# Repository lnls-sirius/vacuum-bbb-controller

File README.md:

# vacuum-bbb-controller
Graphical interface [./software/pydm/pydm_1.2/README.md](./software/pydm/pydm_1.2/README.md)

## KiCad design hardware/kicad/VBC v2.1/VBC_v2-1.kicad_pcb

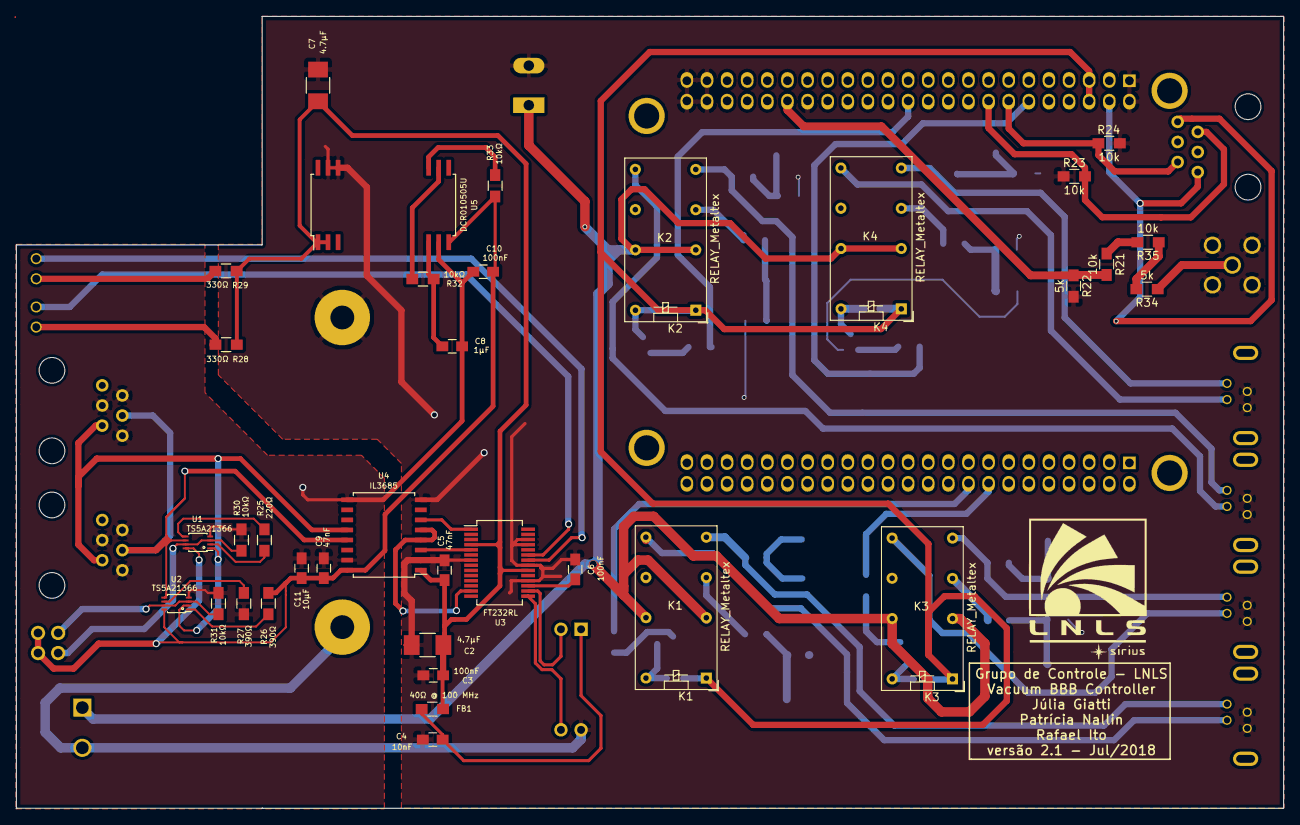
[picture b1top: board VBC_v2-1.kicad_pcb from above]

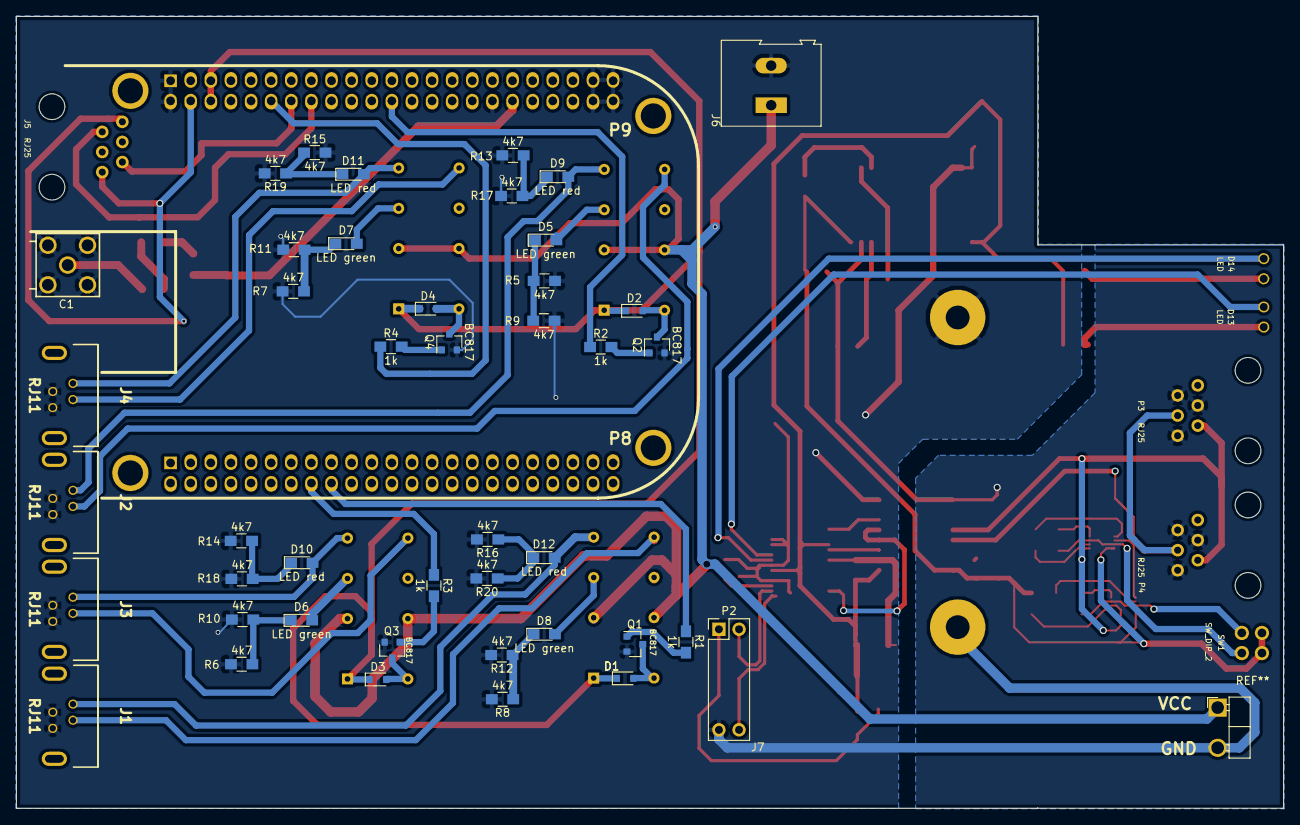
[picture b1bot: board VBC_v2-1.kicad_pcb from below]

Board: 2 copper layers, 160.0 x 100.1 mm, 85 parts (50 on the bottom side), 63 nets.

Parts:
C1: SMA_Molex_73251-2201
C2, C7: 4.7µF; C_1210_HandSoldering
C3, C6, C10: 100nF; C_0805_HandSoldering
C4: 10nF; C_0805_HandSoldering
C5, C9: 47nF; C_0805_HandSoldering
C8: 1µF; C_0805_HandSoldering
C11: 10µF; C_0805_HandSoldering
D1, D2, D3, D4: D; D_0805
D5, D6, D7, D8: LED green; LED_0805_HandSoldering
D9, D10, D11, D12: LED red; LED_0805_HandSoldering
D13, D14: LED; LED_para_painel_KINGBRIGHT
FB1: 40Ω @ 100 MHz; R_0805_HandSoldering
J1, J2, J3, J4: RJ11; RJ11-4P4C-HIROSE_2
J5: RJ25; RJ25_(conversor)
J6: TerminalBlock_Altech_AK300-2_P5.00mm
J7: Conn_01x01; Mean_Well_RS15
K1, K2, K3, K4: RELAY_Metaltex; Relay_DPDT_Omron_G5V-2
P2: USB Mini-B; Pin_Header_Straight_2x06_Pitch2.54mm
P3, P4: RJ25
Q1, Q2, Q3, Q4: BC817; SOT-23
R1, R2, R3, R4: 1k; R_0805_HandSoldering
R5, R6, R7, R8, R9, R10, R11, R12, R13, R14, R15, R16, R17, R18, R19, R20: 4k7; R_0805_HandSoldering
R21, R23, R24, R35: 10k; R_0805_HandSoldering
R22, R34: 5k; R_0805_HandSoldering
R25: 220Ω; R_0805_HandSoldering
R26, R27: 390Ω; R_0805_HandSoldering
R28, R29: 330Ω; R_0805_HandSoldering
R30, R31, R32, R33: 10kΩ; R_0805_HandSoldering
SW1: SW_DIP_2; DIP_switch_(2_positions)
U1, U2: TS5A21366; VSSOP-8
U3: FT232RL; SSOP-28_5.3x10.2mm_Pitch0.65mm
U4: IL3685; SOIC-16_7.5x10.3mm_Pitch1.27mm
U5: DCR010505U

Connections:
+5V: C2.1, C3.1, C5.1, C7.1, FB1.1, R28.1, R29.1, U3.4, U3.20, U4.1, U5.1, U5.2
+24V: J6.1, K1.4, K1.13, K2.4, K2.13, K3.4, K3.13, K4.4, K4.13
/3.3V_BBB: J5.1, J5.6
/AIn_BBB: R21.2, R22.1
/BBB_p5: J5.5, R24.1
/BBB_p6: J5.2, R23.2
/USB_converter_485./5V_ISOLATED: C9.1, C10.1, C11.1, R26.2, R33.1, SW1.1, SW1.3, U1.8, U2.8, U4.16, U5.14
/USB_converter_485./GND_ISOLATED: C8.2, C9.2, C10.2, C11.2, P3.1, P3.4, P3.5, P4.1, P4.4, P4.5, R27.2, R30.1, R31.1, U1.4, U2.4, U4.9, U4.15, U5.13
/USB_converter_485./RS485+: P3.2, P4.2, U1.1, U2.2, U4.12
/USB_converter_485./RS485-: P3.3, P4.3, U1.6, U2.5, U4.13
/USB_converter_485./RXD: U3.5, U4.3
/USB_converter_485./RXLED#: D14.1, U3.22
/USB_converter_485./TXD: U3.1, U4.6
/USB_converter_485./TXDEN: U3.13, U4.4, U4.5
/USB_converter_485./TXLED#: D13.1, U3.23
/USB_converter_485./USB_D+: P2.3, U3.15
/USB_converter_485./USB_D-: P2.2, U3.16
GND: C1.2, C2.2, C3.2, C4.2, C5.2, C6.2, C7.2, J1.2, J1.4, J2.2, J2.4, J3.2, J3.4, J4.2, J4.4, J6.2, J7.1, J7.2, P2.5, Q1.2, Q2.2, Q3.2, Q4.2, R5.2, R6.2, R7.2, R8.2, R9.2, R10.2, R11.2, R12.2, R13.2, R14.2, R15.2, R16.2, R17.2, R18.2, R19.2, R20.2, R22.2, R23.1, R24.2, U3.7, U3.18, U3.21, U3.25, U3.26, U4.2, U4.8, U5.26, U5.27
unnamed: C1.1, R34.1
unnamed: C4.1, FB1.2, P2.1
unnamed: C6.1, U3.17
unnamed: C8.1, R32.1, U5.12
unnamed: D1.2, K1.16, Q1.3
unnamed: D2.2, K2.16, Q2.3
unnamed: D3.2, K3.16, Q3.3
unnamed: D4.2, K4.16, Q4.3
unnamed: D5.1, R5.1, R9.1
unnamed: D5.2, K2.6
unnamed: D6.1, R6.1, R10.1
unnamed: D6.2, K3.6
unnamed: D7.1, R7.1, R11.1
unnamed: D7.2, K4.6
unnamed: D8.1, R8.1, R12.1
unnamed: D8.2, K1.6
unnamed: D9.1, R13.1, R17.1
unnamed: D9.2, J2.1, K2.8
unnamed: D10.1, R14.1, R18.1
unnamed: D10.2, J3.1, K3.8
unnamed: D11.1, R15.1, R19.1
unnamed: D11.2, J4.1, K4.8
unnamed: D12.1, R16.1, R20.1
unnamed: D12.2, J1.1, K1.8
unnamed: D13.2, R28.2
unnamed: D14.2, R29.2
unnamed: J1.3, K1.9
unnamed: J2.3, K2.9
unnamed: J3.3, K3.9
unnamed: J4.3, K4.9
unnamed: Q1.1, R1.2
unnamed: Q2.1, R2.2
unnamed: Q3.1, R3.2
unnamed: Q4.1, R4.2
unnamed: R21.1, R35.2
unnamed: R25.1, U1.2
unnamed: R25.2, U1.5
unnamed: R26.1, U2.1
unnamed: R27.1, U2.6
unnamed: R30.2, SW1.4, U1.3, U1.7
unnamed: R31.2, SW1.2, U2.3, U2.7
unnamed: R32.2, U5.16
unnamed: R33.2, U5.17
unnamed: R34.2, R35.1
VCC: D1.1, D2.1, D3.1, D4.1, K1.1, K2.1, K3.1, K4.1

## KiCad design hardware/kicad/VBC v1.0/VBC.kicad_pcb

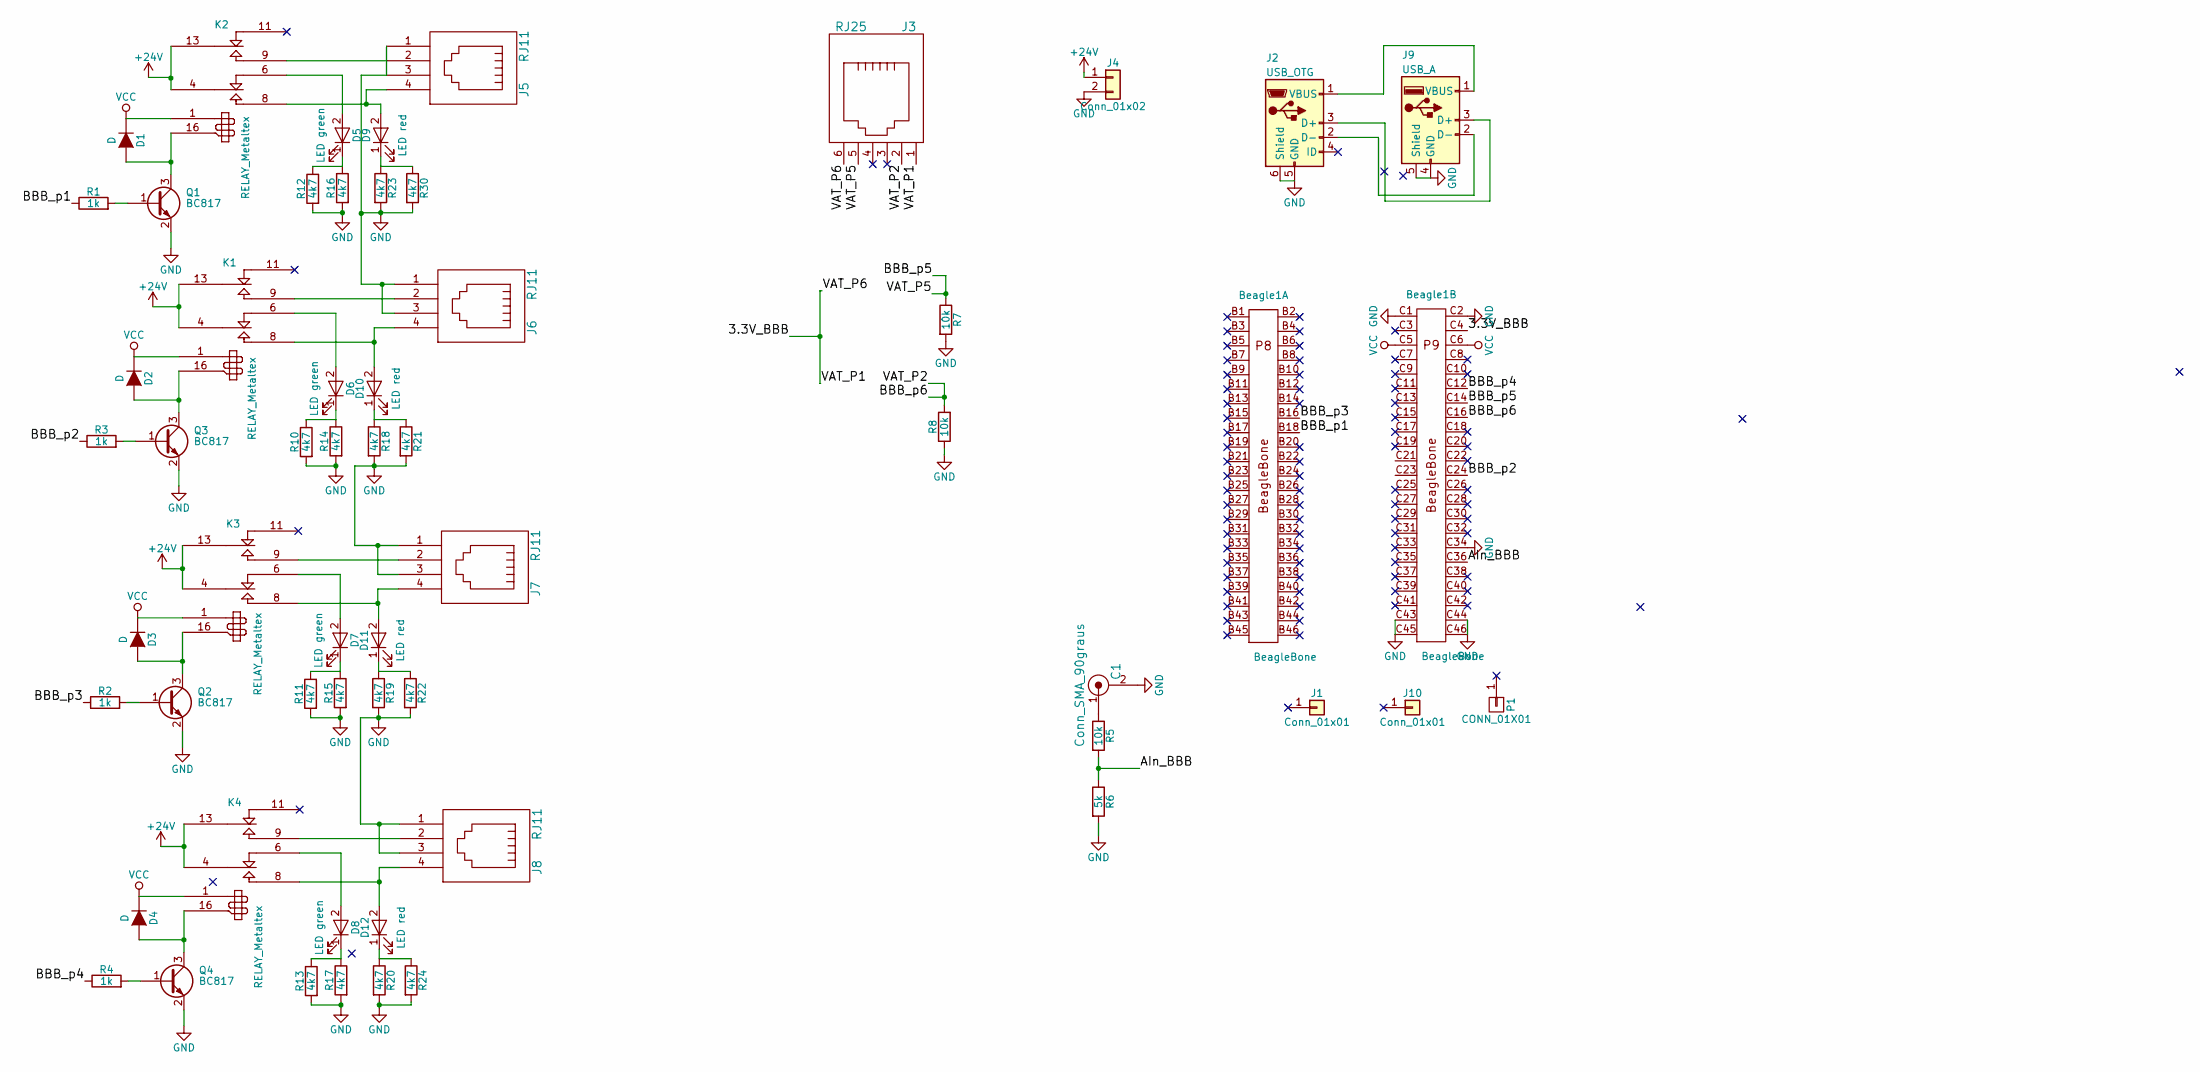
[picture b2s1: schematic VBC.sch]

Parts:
Beagle1: BeagleBone; BEAGLEBONEBLACK
C1: Conn_SMA_90graus; SMA_THT_Jack_Straight
D1, D2, D3, D4: D; D_0805
D5, D6, D7, D8: LED green; LED_0805_HandSoldering
D9, D10, D11, D12: LED red; LED_0805_HandSoldering
J1: Conn_01x01; Mean_Well_RS15
J2: USB_OTG; USB_Micro-B
J3: RJ25; RJ25_(conversor)
J4: Conn_01x02; TerminalBlock_Altech_AK300-2_P5.00mm
J5, J6, J7, J8: RJ11; RJ11-4P4C-HIROSE
J9: USB_A
J10: Conn_01x01; BEAGLEBONEBLACK_(fixation_holes)
K1, K2, K3, K4: RELAY_Metaltex; Relay_DPDT_Omron_G5V-2
P1: CONN_01X01; LNLS_LOGO
Q1, Q2, Q3: BC817; SOT-23
Q4: BC817; R_0805_HandSoldering
R1, R2, R3, R4: 1k; R_0805_HandSoldering
R5, R7, R8: 10k; R_0805_HandSoldering
R6: 5k; R_0805_HandSoldering
R10, R11, R12, R13, R14, R15, R16, R17, R18, R19, R20, R21, R22, R23, R24: 4k7; R_0805_HandSoldering
R30: 4k7; R_0805

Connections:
+24V: J4.1, K1.4 (C1), K1.13 (C2), K2.4 (C1), K2.13 (C2), K3.4 (C1), K3.13 (C2), K4.4 (C1), K4.13 (C2)
/3.3V_BBB: Beagle1.C4, J3.1, J3.6
/AIn_BBB: Beagle1.C36, R5.2, R6.1
/BBB_p1: Beagle1.B18, R1.1
/BBB_p2: Beagle1.C24, R3.1
/BBB_p3: Beagle1.B16, R2.1
/BBB_p4: Beagle1.C12 (B12), R4.1
/BBB_p5: Beagle1.C14, J3.5, R7.1
/BBB_p6: Beagle1.C16, J3.2, R8.2
GND: Beagle1.C1, Beagle1.C2, Beagle1.C34, Beagle1.C43, Beagle1.C44, Beagle1.C45, Beagle1.C46, C1.2, J2.5 (GND), J2.6 (Shield), J4.2, J5.1, J5.3, J6.1, J6.3, J7.1, J7.3, J8.1, J8.3, J9.4 (GND), J9.5 (Shield), Q1.2 (E), Q2.2 (E), Q3.2 (E), Q4.2 (E), R6.2, R7.2, R8.1, R10.2, R11.2, R12.2, R13.2, R14.2, R15.2, R16.2, R17.2, R18.2, R19.2, R20.2, R21.2, R22.2, R23.2, R24.2, R30.2
unnamed: C1.1, R5.1
unnamed: D1.2 (A), K2.16, Q1.3 (C)
unnamed: D2.2 (A), K1.16, Q3.3 (C)
unnamed: D3.2 (A), K3.16, Q2.3 (C)
unnamed: D4.2 (A), K4.16, Q4.3 (C)
unnamed: D5.1 (K), R12.1, R16.1
unnamed: D5.2 (A), K2.6 (R1)
unnamed: D6.1 (K), R10.1, R14.1
unnamed: D6.2 (A), K1.6 (R1)
unnamed: D7.1 (K), R11.1, R15.1
unnamed: D7.2 (A), K3.6 (R1)
unnamed: D8.1 (K), R13.1, R17.1
unnamed: D8.2 (A), K4.6 (R1)
unnamed: D9.1 (K), R23.1, R30.1
unnamed: D9.2 (A), J5.4, K2.8 (T1)
unnamed: D10.1 (K), R18.1, R21.1
unnamed: D10.2 (A), J6.4, K1.8 (T1)
unnamed: D11.1 (K), R19.1, R22.1
unnamed: D11.2 (A), J7.4, K3.8 (T1)
unnamed: D12.1 (K), R20.1, R24.1
unnamed: D12.2 (A), J8.4, K4.8 (T1)
unnamed: J2.1 (VBUS), J9.1 (VBUS)
unnamed: J2.2 (D-), J9.2 (D-)
unnamed: J2.3 (D+), J9.3 (D+)
unnamed: J5.2, K2.9 (T2)
unnamed: J6.2, K1.9 (T2)
unnamed: J7.2, K3.9 (T2)
unnamed: J8.2, K4.9 (T2)
unnamed: Q1.1 (B), R1.2
unnamed: Q2.1 (B), R2.2
unnamed: Q3.1 (B), R3.2
unnamed: Q4.1 (B), R4.2
VCC: Beagle1.C5, Beagle1.C6, D1.1 (K), D2.1 (K), D3.1 (K), D4.1 (K), K1.1, K2.1, K3.1, K4.1

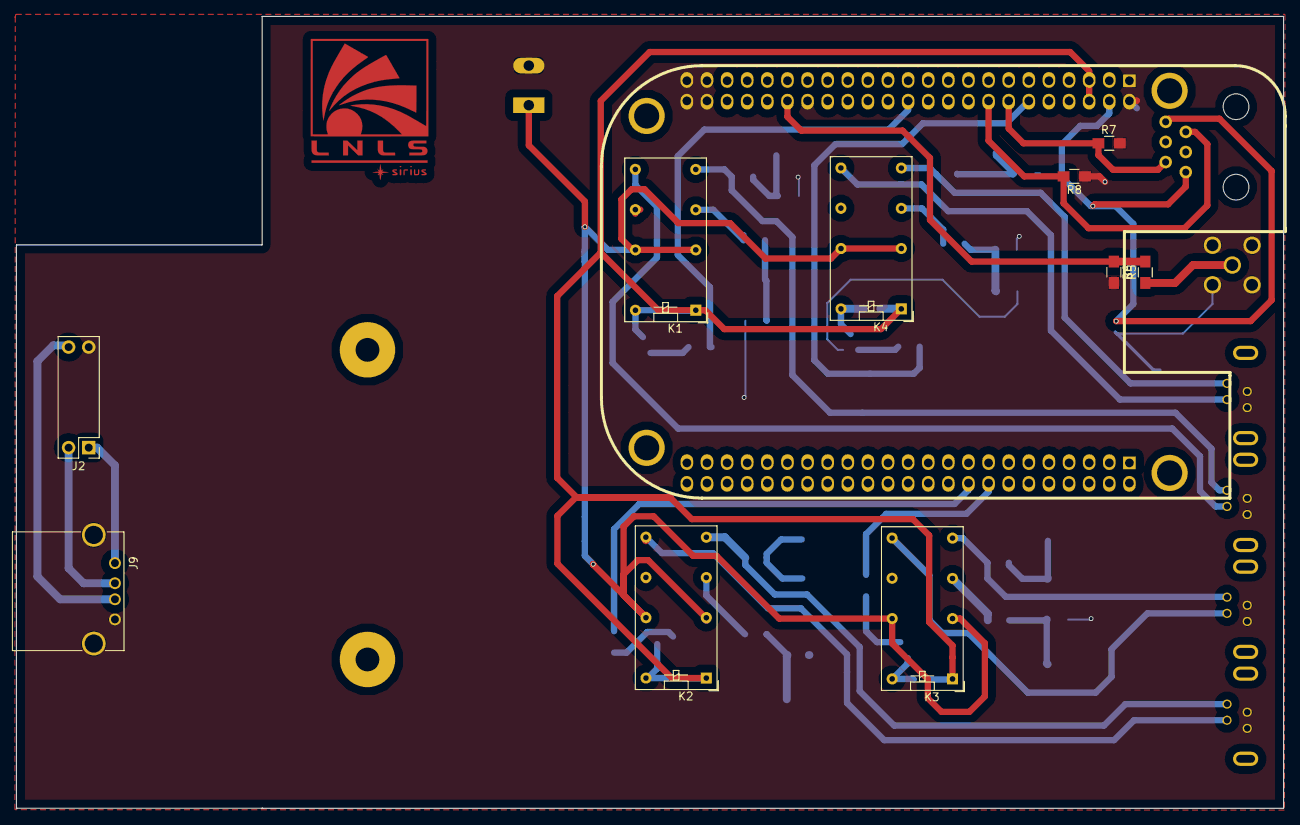
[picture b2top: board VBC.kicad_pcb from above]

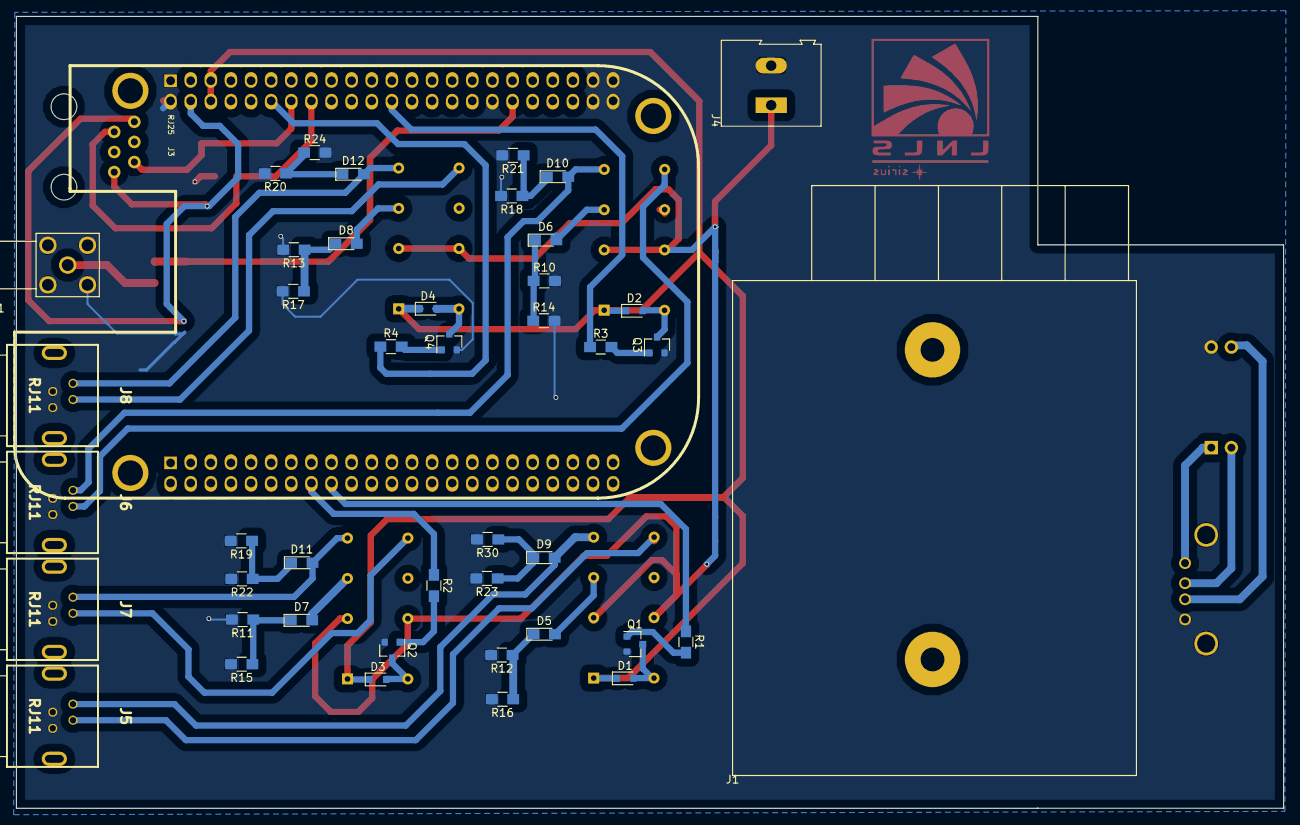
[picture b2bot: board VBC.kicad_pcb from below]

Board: 2 copper layers, 160.0 x 100.1 mm, 57 parts (45 on the bottom side), 43 nets.

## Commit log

2018-06-14 updated hardware files
2018-06-18 ACP 15 software support for RS-485 communication added
2018-06-26 TURBOVAC software support for RS-485 communication added
2018-06-26 added TURBOVAC cable connection and updated ACP cable connection
2018-06-26 equipment documents and datasheets added
2018-06-26 repository reorganization
2018-06-28 functions added to turbovac code
2018-07-02 added relay LED status in schematic
2018-07-02 new hardware version
2018-07-06 updated ACP and TURBOVAC libraries and unix socket for IOC
2018-07-06 updated turbovac.py file
2018-07-10 added EPICS support for valves controls under unix socket
2018-07-11 IOC files added (cmd, db, proto)
2018-07-11 added TURBOVAC support in unix socket for IOC
2018-07-11 first pydm ui released
2018-07-12 minor changes in hardware files
2018-07-16 updated unix socket for IOC
2018-07-16 pydm ui version 1.1 released (generic task telegram communication)
2018-07-16 included telegram stream for TURBOVAC support
2018-07-16 added '390 Micro-Ion ATM' documentation
2018-07-16 updated BBB pins fou updated hardware version
2018-07-18 main window UI added
2018-07-18 added support for analog reading (pressure)
2018-07-18 IOC files updated
2018-07-18 new hardware version - v2.0
2018-07-18 updated hardware version
2018-07-18 hardware version 1.0
2018-07-18 updated hardware version 2.0
2018-07-18 added status PVs for process scripts; added thread support and split the code in two threads
2018-07-18 added process scripts to turn on/off the system
2018-07-19 added logo files for UI and PV name list
2018-07-19 updated socket unix file
2018-07-19 updated process scripts and unix socket
2018-07-25 updated hardware version 2.1
2018-07-26 added process scripts for GUI
2018-07-27 adicionando paineis v2.1
2018-07-31 added support for parameterized process scripts
2018-07-31 main window with all vacuum car status added and minor fixes in the other windows
2018-07-31 parameterized PVs names and power of ten representation por pressure values added
2018-08-08 added other ui windows
2018-08-08 updated ui windows and python scripts
2018-08-08 created other python scripts for GUI
2018-08-09 pydm directory reorganized
2018-08-13 added cable file
2018-08-16 v1.1 user interface added (using layouts)
2018-08-16 fixed path for python scripts
2018-08-16 signals created for v1.1 ui
2018-08-17 updated cable file
2018-08-17 added suport for launching .ui files with python
2018-08-17 python files for launching ui added
2018-08-20 added files about the power supply box
2018-08-20 updated files about the power supply box
2018-08-23 repo reorganization & files updated
2018-09-05 Hardware PDF file added
2018-09-14 fixed Windows/Linux incompatibilities for PyDM 1.2 release
2018-09-17 started support for PyDM 1.4
2018-09-20 valve confirmation message width adjusted
2018-09-20 directories renamed
2018-09-20 desktop file for VM added
2018-09-20 minor changes
2018-09-21 vbc_unix_socket.py updated
2018-09-24 minor changes updated
2018-09-25 new features added
2018-09-28 added "initialization.py" script
2018-09-28 updated unix socket: write value 600 in parameter 28 at initialization (TURBOVAC)
2018-10-01 fixed missing libca.so for initialization.py script
2018-10-02 minor changes to the project
2018-10-09 error fixed
2018-10-10 "simple_window" ui added
2018-10-10 fixed "process_recovery" script call under "run-IOC.sh"
2018-10-15 fixed "simple_window.ui"
2018-10-16 added support for Internet sharing with BBB
2018-11-26 added VBC v2.2 files
2018-11-26 recconection attempt, logging and queue system added
2019-02-01 changed logging message
2019-03-29 docker support added
2019-03-29 docker-compose.yml changed to run with docker compose instead of swarm
2019-03-29 added VBC.bat for launching docker-compose
2019-03-29 added compose file for Windows (env DISPLAY adjusted)
2019-04-01 EPICS_CA_ADDR_LIST edited
2019-04-03 docker files modified
2019-04-03 Windows icon added
2019-04-03 batch file VBC.bat updated: wait for docker daemon to start
2019-04-03 Windows shortcut added
2019-04-04 Windows VcXsrv config file added
2019-04-05 divided docker support in Linux/Windows
2019-04-09 changed documentation dir
2019-04-09 Agilent valve doc renamed
2019-04-10 Hammond enclosure datasheet added
2019-04-10 documentation pcb images added
2019-04-23 path to windows files fixed
2019-04-25 path to windows docker files fixed in bat script
2019-06-26 VM icon added
2019-11-21 added confirmation message to venting valve operations
2021-05-13 Include ps1 start script
2021-05-13 pydm1.2/ include README and requirements
2021-05-13 Bump py from 1.8.0 to 1.10.0 in /software/pydm/pydm_1.2
    Bumps [py](https://github.com/pytest-dev/py) from 1.8.0 to 1.10.0.
    - [Release notes](https://github.com/pytest-dev/py/releases)
    - [Changelog](https://github.com/pytest-dev/py/blob/master/CHANGELOG.rst)
    - [Commits](https://github.com/pytest-dev/py/compare/1.8.0...1.10.0)
2021-05-13 Bump pyxdg from 0.25 to 0.26 in /software/pydm/pydm_1.2
    Bumps [pyxdg](https://github.com/takluyver/pyxdg) from 0.25 to 0.26.
    - [Release notes](https://github.com/takluyver/pyxdg/releases)
    - [Changelog](https://github.com/takluyver/pyxdg/blob/master/ChangeLog)
    - [Commits](https://github.com/takluyver/pyxdg/compare/rel-0.25...rel-0.26)
2021-05-13 Bump psutil from 5.6.5 to 5.6.6 in /software/pydm/pydm_1.2
    Bumps [psutil](https://github.com/giampaolo/psutil) from 5.6.5 to 5.6.6.
    - [Release notes](https://github.com/giampaolo/psutil/releases)
    - [Changelog](https://github.com/giampaolo/psutil/blob/master/HISTORY.rst)
    - [Commits](https://github.com/giampaolo/psutil/compare/release-5.6.5...release-5.6.6)
2021-05-13 Bump urllib3 from 1.25.7 to 1.25.8 in /software/pydm/pydm_1.2
    Bumps [urllib3](https://github.com/urllib3/urllib3) from 1.25.7 to 1.25.8.
    - [Release notes](https://github.com/urllib3/urllib3/releases)
    - [Changelog](https://github.com/urllib3/urllib3/blob/main/CHANGES.rst)
    - [Commits](https://github.com/urllib3/urllib3/compare/1.25.7...1.25.8)
2021-05-13 Bump cryptography from 1.7.1 to 3.3.2 in /software/pydm/pydm_1.2
    Bumps [cryptography](https://github.com/pyca/cryptography) from 1.7.1 to 3.3.2.
    - [Release notes](https://github.com/pyca/cryptography/releases)
    - [Changelog](https://github.com/pyca/cryptography/blob/main/CHANGELOG.rst)
    - [Commits](https://github.com/pyca/cryptography/compare/1.7.1...3.3.2)
2021-05-13 windows docs
2021-05-13 Script using pythonw
2021-05-13 Include custom launcher
2021-05-13 Update .ps1 scripts
2021-05-13 Update README and requiremnets
2021-05-13 start.ps1/ using pythonw
2021-05-14 update pydm_1.2/README
